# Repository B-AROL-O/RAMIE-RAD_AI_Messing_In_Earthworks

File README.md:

---
title: RAMIE-RAD AI Messing In Earthworks
emoji: 🐨
colorFrom: gray
colorTo: pink
sdk: gradio
sdk_version: 5.49.1
app_file: app.py
pinned: false
license: cc-by-sa-4.0
short_description: A local Gradio MCP server controlling a robot platform
tags:
  - mcp-in-action-track-creative
---

# RAMIE

- **Radical**
- **AI**
- **Messing**
- **In**
- **Earthworks**

A local Gradio MCP AI powered wheeled robot, capable of listening, speaking and executing commands, in the vision of the B-AROL-O team

*TRIVIA: The B-AROL-O team likes to use names of Italian wines as acronyms for robots. [RAMIE](https://nebbiaeluce.com/producer/ramie-perosa-argentina/) is a local red wine from my village*

*TRIVIA: "Vino" is the Italian word for Wine. Intel OpenVINO AI runtime is the perfect runtime to run a robot named after an italian wine by italian developers*

## Scope

The scope of this repository is to document the Hugging Face MCP 1° birthday hackathon

The scope of this repository is to document all instruction to replicate in full the robot project

Work is divided in two parts:

- Work that is qualifying for the hackathon itself, that was started 2025-11-14, this includes learning GRADIO, learning MPC, preparing the MCP tools, interfacing ollama with AI models needed

- Work that is not qualifying for the hackathon and was recycled from previous projects and is in this repository in order to make a complete set of instructions to replicate this project. This include the electronics, the mechanical part of the robot, learning the compute board, and learning that was done for ollama testing of the microphone

This felt like a good chance to gather all the disparate documentation and work done over the years in one tidy set of insttructions that can be followed to make one complete platform end to end with the GRADIO/MCP/OLLAMA software being the keystone that glue it all together.

# Documentation

Designs marked with '*(not qualifying for hackathon)* ' are older recycled design that are here for documentation, instruction and completeness purposes and are not qualifying for the scope of the hackathon.  They are either taken as is, or lightly/heavily adapted to serve for the scope of the Hackathon.

## Mechanical Design

I design in OpenSCAD as I like making geometries as code and I like doing everything parametric.

I decided that the robots should be powered by 18650 batteries. Target configuration is 2S2P. For RAMIE I went with an inverted design that is soldered 4S1P to get 14.8V nominal voltage to be compatible with the input regulator for the Latte Panda Lite Board.

- [MEC: 18650 Battery Holder](/Mechanical/Battery%20Holder%2018650%20OpenSCAD) *(not qualifying for hackathon)*
- [MEC: Wheeled Platform](/Mechanical/Wheeled%20Platform%20OpenSCAD) *(not qualifying for hackathon)*

The robot platform is the one I am designing for Latte Panda Lite Board powered AI robots, it was a good fit for this hackathon

## Board Motor Screen

Interfaces with a UART bidirectional link with the SBC, answer to a serial protocol, controls two servos and a LCD screen. Choosen because I had a bounch assembled in a drawer and working firmware to start from.

- [ELN: Board Motor Screen](/Electronics/Board%20motor%20screen) *(not qualifying for hackathon)*
- [FW: Board Motor Screen](/Firmware/Motor%20Board%20Atmel%20AT324PA) *(not qualifying for hackathon)*
- [FW: Test Bench Serial Communication](/Firmware/Test%20Bench%20Parser) *(not qualifying for hackathon)*
- [FW: Test Bench Motion Orchestrator](/Firmware/Test%20bench%20motion%20orchestration)
- [SW: Python demos to test communication between Host computer and board](/Software/Demo_Host_Serial_Communication/)
- [SW: Python demos to test communication between SBC and board](/Software/Demo_SBC_Serial_Communication/)

# SBC Latte Panda Mu N100 16GB

I lost count of the SBCs I tested for my ultimate goal of making a general robot that expresses a degree of general intelligence with local compute only. The N100 16GB could be it, it has the memory, bandwidth, compute and power envelope to run useful LLMs on the go.

## Luckfox PicoKVM

I always have trouble accessing SBC headless, I finally got a 49€ KVM to mitigate the issue and free myself from using discrete keyboard and mouse

[Luckfox PicoKVM Instructions](/Software/Luckfox%20PicoKVM)

## INSTALL UBUNTU

Install Ubuntu 24.04 Server LTS on the SBC and configure network and storage

[Ubuntu 24.04 Server Install Instructions](/Software/Ubuntu%2024_04%20server%20LTS)

## Luckfox PicoKVM

I always have trouble accessing SBC headless, I finally got a 49€ KVM to mitigate the issue and free myself from using discrete keyboard and mouse

[Luckfox PicoKVM Instructions](/Software/Luckfox%20PicoKVM)

## TTYS0 SSH PUTTY SERIAL

Configure the GRUB to use ttyS0 as UART serial interface to let the host connect via putty via USB to UART FTDI adapter

[TTYS0 SERIAL GRUB CONFIGURATION](/Software/ttys0%20SSH)

## VS Code Remote

Use VS code on host machine with remote SSH plugin to evelop and run code directly on the SBC via WiFi radio

[VS Code Remote Instructions](/Software/VS%20Code%20Remote%20Development%20on%20SBC)

# Battery Teleoperation SSH WiFI

Final test with the robot under battery power with SBC, AT324, WiFI and motors running with SSH teleoperation form keyboard

https://github.com/user-attachments/assets/86d634cf-5507-45de-8ebf-013d29c1c32a

# Ollama GRADIO LLamaindex

The robot hosts and run locally GRADIO

There are two chats

One is the chat to ask about RAMIE capability using LLamaindex to rag the specifications

The second has a tool that attaches with a MCP tool to the motors and genereate serial command for the robot to execute

# Contributors

- [Orso Eric](https://github.com/OrsoEric)

## Useful Links

- [Huggingface Hackathon](https://huggingface.co/MCP-1st-Birthday) 
- [Huggingface Example Track 2 Creative](https://huggingface.co/spaces/ysharma/sample5-hackathon-space-submission/blob/main/README.md)
- [Huggingface space](https://huggingface.co/spaces/MCP-1st-Birthday/RAMIE-RAD_AI_Messing_In_Earthworks)
- [Huggingface Organization](https://huggingface.co/RAMIE-RAD-AI-Messing-In-Earthworks)
- [Github repository](https://github.com/B-AROL-O/RAMIE-RAD_AI_Messing_In_Earthworks)
- [Github project board](https://github.com/orgs/B-AROL-O/projects/5)

## TRACK

Track 2: MCP in Action

mcp-in-action-track-creative

# Copyright and License

Copyright (C) 2025, B-AROL-O Team, all rights reserved.

NOTE: This repository is based upon https://github.com/arol-polito/python-project-template.
Source code license

The source code contained in this repository and the executable distributions are licensed under the terms of the MIT license as detailed in the LICENSE file.
Documentation license

CC BY-SA 4.0

Please note that your contribution to the project Documentation is licensed under a Creative Commons Attribution-Share Alike 4.0 License. see https://creativecommons.org/licenses/by-sa/4.0/

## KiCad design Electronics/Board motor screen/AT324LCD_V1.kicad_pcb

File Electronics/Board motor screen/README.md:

# Motor Board

This is a board that I designed in 2012 to control robots

It was convenient for me to use this board as I have a bounch of them assembled

It has an Atmel AT324PA PDIP40, an ISP programmer, power and breaks out all the pins

I also have a more recent board based on Atmel 4809 in SMD package, both work for this application.

## Gerber

### Bottom Side

### Top Side

### Top Components 

### Bot Components 

### Assembled Powered Flashed

## Adapters

For going to the board I soldered a number of adapters

### Adapter - Pinstrip to Eight Servo

TODO

### Adapter - Pinstrip to Screw COnnector

TODO

## BOM - Bill of Material

TODO

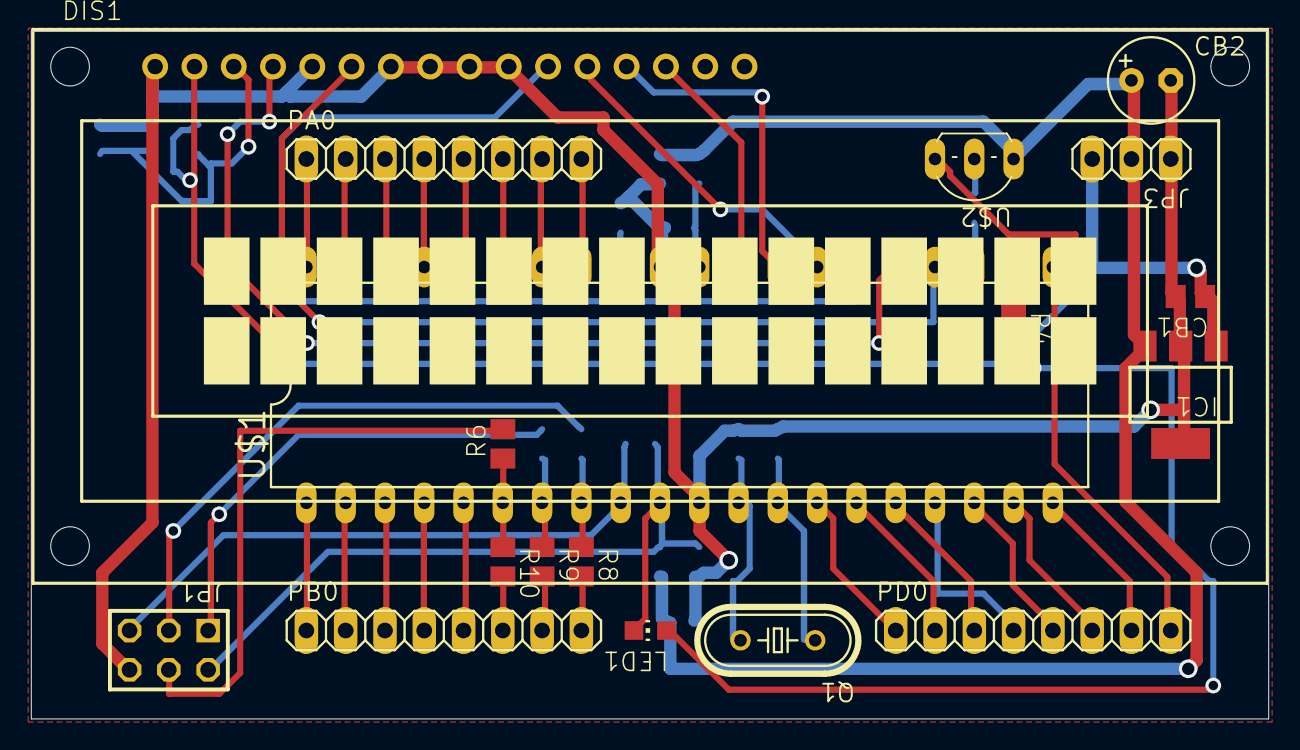
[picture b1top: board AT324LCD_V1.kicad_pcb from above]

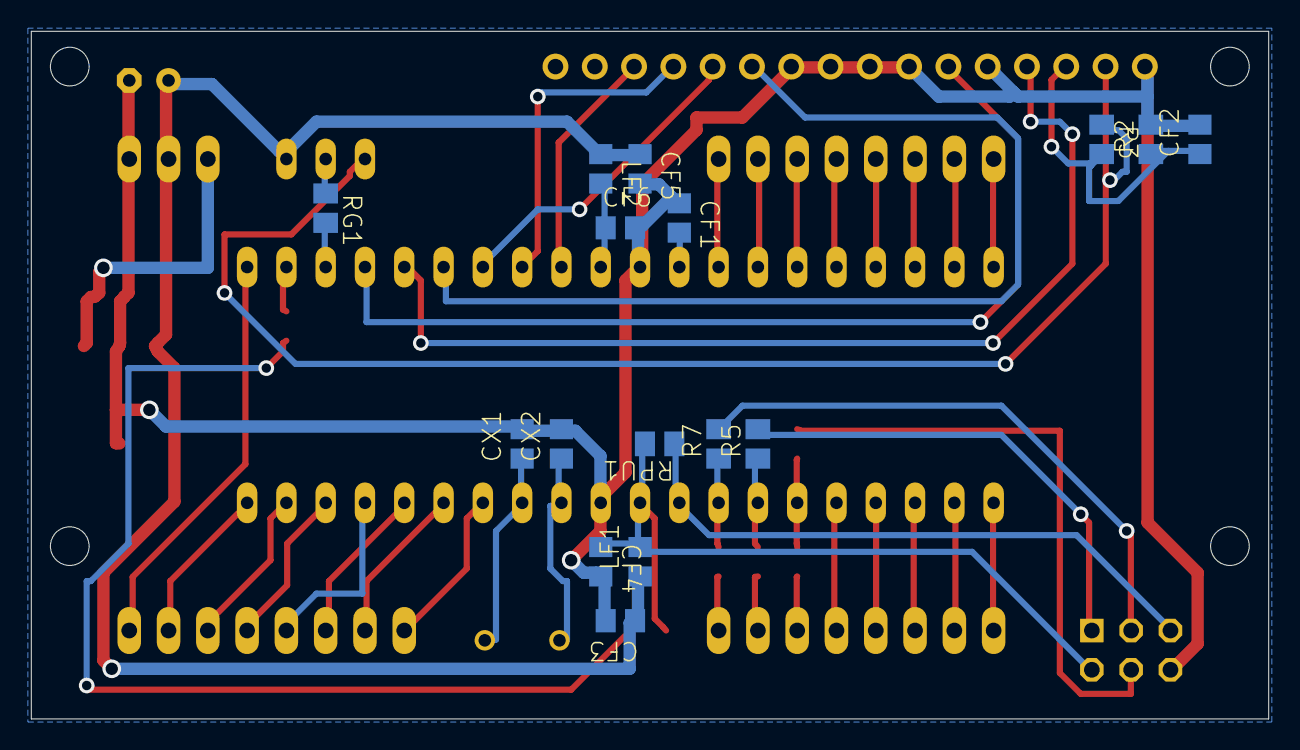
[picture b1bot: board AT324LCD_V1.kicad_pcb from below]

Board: 16 copper layers, 80.0 x 44.5 mm, 34 parts (16 on the bottom side), 51 nets.

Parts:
CB1: 1u; C0805
CB2: 100u; E2,5-6
CF1, CF2: 10n; C0805
CF3, CF4, CF5, CF6: 100n; C0805
CX1, CX2: 22p; C0805
DIS1: TUXGR_16X2_R2
IC1: SOT223
JP1: AVR-ISP-6
JP3: 1X03
LED1: CHIP-LED0805
LF1, LF2: 600; L0805
PA0: 1X08
PB0: 1X08
PD0: 1X08
Q1: 20M; HC49_S
R2, R5, R6, R7, R8, R9, R10: 1k; M0805
R3: 8.2k; M0805
R4: 330; M0805
RG1: 4.7; M0805
RPU1: 8.2k; M0805
U$1: MEGA324PDIL40; DIL40
U$2: ZVP2106TO92; TO92-

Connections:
D4: DIS1.11, U$1.26
D5: DIS1.12, U$1.27
D6: DIS1.13, U$1.28
D7: DIS1.14, U$1.29
EN: DIS1.6, U$1.24
GND: CB1.2, CB2.-, CF1.1, CF2.2, CF3.2, CF4.2, CF5.2, CF6.2, CX1.2, CX2.2, DIS1.1, DIS1.5, DIS1.7, DIS1.8, DIS1.9, DIS1.10, IC1.2, IC1.4, JP1.6, JP3.1, R2.2, U$1.11, U$1.31
LCDEN#: RG1.2, U$1.23
LED: R4.1, U$1.22
unnamed: CF1.2, U$1.32
unnamed: CX1.1, Q1.1, U$1.13
unnamed: CX2.1, Q1.2, U$1.12
unnamed: PB0.8, R8.2
unnamed: RG1.1, U$2.2
unnamed: CF2.1, DIS1.3, R2.1, R3.2
unnamed: LED1.A, R4.2
unnamed: PB0.7, R9.2
unnamed: PB0.6, R10.2
unnamed: JP1.1, R5.2
unnamed: JP1.4, R6.2
unnamed: JP1.3, R7.2
PA0: PA0.1, U$1.40
PA1: PA0.2, U$1.39
PA2: PA0.3, U$1.38
PA3: PA0.4, U$1.37
PA4: PA0.5, U$1.36
PA5: PA0.6, U$1.35
PA6: PA0.7, U$1.34
PA7: PA0.8, U$1.33
PB0: PB0.1, U$1.1
PB1: PB0.2, U$1.2
PB2: PB0.3, U$1.3
PB3: PB0.4, U$1.4
PB4: PB0.5, U$1.5
PB5: R6.1, R10.1, U$1.6
PB6: R5.1, R9.1, U$1.7
PB7: R7.1, R8.1, U$1.8
PD0: PD0.1, U$1.14
PD1: PD0.2, U$1.15
PD2: PD0.3, U$1.16
PD3: PD0.4, U$1.17
PD4: PD0.5, U$1.18
PD5: PD0.6, U$1.19
PD6: PD0.7, U$1.20
PD7: PD0.8, U$1.21
RS: DIS1.4, U$1.25
RST#: JP1.5, RPU1.1, U$1.9
VADC: CF6.1, LF2.2, U$1.30
VIN: CB1.1, IC1.1, JP3.3
VIN5: CB2.+, CF3.1, CF5.1, IC1.3, JP3.2, LF1.1, LF2.1, U$2.3
VLCD: DIS1.2, R3.1, U$2.1
VUC: CF4.1, JP1.2, LED1.C, LF1.2, RPU1.2, U$1.10

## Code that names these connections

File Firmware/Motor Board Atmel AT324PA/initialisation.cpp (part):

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	///	configure the related I/O pin as output
	///**********************************************************************

	//PA0			: Servo 0
	//PA1			: Servo 1
	//PA2			: Servo 2
	//PA3			: Servo 3
	//PA4			: Servo 4
	//PA5			: Servo 5
	//PA6			: Servo 6
	//PA7			:
	PORT_A_CONFIG('L','L','L','L','L','L','L','L');
	

	//PB0			:
	//PB1			:
	//PB2			:
	//PB3			:
	//PB4			:
	//PB5			:
	//PB6			:
	//PB7			:
	PORT_B_CONFIG('R','R','R','R','R','R','R','R');

	//PC0			: LED#
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	//PC7			: LCD_D7
	PORT_C_CONFIG('H','H','L','L','L','L','L','L');

	//PD0			: UC_RXI SBC_TXO 
	//PD1			: UC_TXO SBC_RXI
	//PD2			: 
	//PD3			:
	//PD4			:
	//PD5			:
	//PD6			:
	//PD7			:
	PORT_D_CONFIG('R','H','R','R','R','R','R','R');

	///**********************************************************************
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
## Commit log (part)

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2025-11-14 Update README with Huggingface and GitHub links
    Added links to Huggingface space, organization, and GitHub repository.
2025-11-15 Adding github project and partecipant
2025-11-15 add ,.license
2025-11-15 Added link for track Added folder structure
2025-11-15 added readme to folder structure
2025-11-15 This is a board that I designed in 2012 to control robots It was convenient for me to use this board as I have a bounch of them assembled It has an Atmel AT324PA, an ISP programmer, power and breaks 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
2025-11-15 Added images and documentation for the motor control board
2025-11-15 Adapted from Unit Zero (2019) and Industrious Resonance (2025)
    Firmware to control the motor Board
    PPM signal for continuous rotation servo motors
    LCD screen with parallel protocol
    UART link to communicate with SBC
    TODO: Develop a communication protocol that works with MCP server GRADIO
    https://github.com/B-AROL-O/RAMIE-RAD_AI_Messing_In_Earthworks/issues/5
2025-11-15 Added firmware links to the main README Added some more description on the readme https://github.com/B-AROL-O/RAMIE-RAD_AI_Messing_In_Earthworks/issues/5 https://github.com/B-AROL-O/RAMIE-RAD_AI_Mess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
2025-11-15 Added documentation of the firmware
    https://github.com/B-AROL-O/RAMIE-RAD_AI_Messing_In_Earthworks/issues/5
2025-11-15 Test bench for the serial communicaton and callback function on Firmware https://github.com/B-AROL-O/RAMIE-RAD_AI_Messing_In_Earthworks/issues/5
2025-11-15 linked test bench readme on the main readme https://github.com/B-AROL-O/RAMIE-RAD_AI_Messing_In_Earthworks/issues/1
2025-11-15 Added the codeblock test bench for motion orchestration class. https://github.com/B-AROL-O/RAMIE-RAD_AI_Messing_In_Earthworks/issues/5
2025-11-15 OpenSCAD Holder for 18650 batteries developed over several years
    Configurations
    - 1S1P
    - 2S1P
    - 2S2P
    - 2S2P upside down
    https://github.com/B-AROL-O/RAMIE-RAD_AI_Messing_In_Earthworks/issues/10
2025-11-15 Fixed readme for the battery holder https://github.com/B-AROL-O/RAMIE-RAD_AI_Messing_In_Earthworks/issues/10 https://github.com/B-AROL-O/RAMIE-RAD_AI_Messing_In_Earthworks/issues/1
2025-11-15 OpenSCAD design of the platform This is recycled from Industrious Resonance that is already a Latte Panda Mu platform under development I do need to refine it as it was not finished https://github.co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
2025-11-15 Added images of the design process of the wheeled platform. This was lots of work I did for Industrious Resonance but it worked out great I have a pivot ping pong ball, HS422 servo holders, all tolle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
    TODO: geometry for the electronics and details. I decided to print an intermediate step.
2025-11-15 Added documentation of the platform design process and updated readme https://github.com/B-AROL-O/RAMIE-RAD_AI_Messing_In_Earthworks/issues/8
2025-11-15 BUG: if I have a command with argument VR%L% and a command VR%L%T% the parser gets confused and cannot match.
2025-11-15 doesn't compile. something with C++? -.-
2025-11-15 I rebuilt the AVR project using the C++ compiler and it compiles and load now Much bigger executable from 3 to 9KB so it's doing more Linked the parser Seems to be doing something But the serial deco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
2025-11-15 FRACK YEAH it works! I had just some issue with initialization. Done a video and tested ping and speed commands and they work. The F signature command doesn't, it's likely an infinite loop. I didn't 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
    https://github.com/B-AROL-O/RAMIE-RAD_AI_Messing_In_Earthworks/issues/5
2025-11-15 https://github.com/B-AROL-O/RAMIE-RAD_AI_Messing_In_Earthworks/issues/1
2025-11-16 Remove borked project and rename the working project
2025-11-16 Fixed SIGN and REV messages. Added aid function to send strings. https://github.com/B-AROL-O/RAMIE-RAD_AI_Messing_In_Earthworks/issues/5
    Documentation for the communication protocol.
    https://github.com/B-AROL-O/RAMIE-RAD_AI_Messing_In_Earthworks/issues/6
2025-11-16 DEMO 3 The code sends every 250ms increase speed on R by increment of 10 up to 50 Then decrement in speed -10 down to -50 then increment of +10 up to 0 then do the same on L speed repeat
    https://github.com/B-AROL-O/RAMIE-RAD_AI_Messing_In_Earthworks/issues/15
2025-11-16 Linked Python demo to the board section main README https://github.com/B-AROL-O/RAMIE-RAD_AI_Messing_In_Earthworks/issues/1 https://github.com/B-AROL-O/RAMIE-RAD_AI_Messing_In_Earthworks/issues/15
2025-11-16 Added a demo inside the firmware that loads commands into the UART RX buffer directly
    This way I can test the parser without using the terminal.
    https://github.com/B-AROL-O/RAMIE-RAD_AI_Messing_In_Earthworks/issues/18
2025-11-16 adding an executed command counter on the LCD importing the motion orchestration c++ library
2025-11-16 implemented //Enumerates modes of operation of the servo motors enum E_servo_mode { //Direct speed mode will sustain the speed given until different instruction SERVO_SPEED_MODE, //Timed servo mode w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
    when sending a direct speed command goes into DS and sustain last speed
    when sending a timed speed, goes into TS mode and use the orchestrator, if the queue is empty, it stops moving
    https://github.com/B-AROL-O/RAMIE-RAD_AI_Messing_In_Earthworks/issues/18
2025-11-16 Orchestrator is linked but seems not to be working...
2025-11-16 Firmware for motion orchestration done, filmed video Showed switch between DS and TS Showed loading of the queue and timed execution
    https://github.com/B-AROL-O/RAMIE-RAD_AI_Messing_In_Earthworks/issues/18
2025-11-16 Added images and videos of the testing for the firmware and serial interface
    https://github.com/B-AROL-O/RAMIE-RAD_AI_Messing_In_Earthworks/issues/18
2025-11-17 Used kicad to convert and measure the AT324 board In Openscad modelling the sloped support wall Done the trigonometry to decide on the board angle
2025-11-17 Building the mechanical support for AT324 I did a lot of fancy trigonometry to find where to drill
2025-11-17 Did precision drills for the screw! TODO: Now I just need to tip them with an hole for the nut
2025-11-17 Added initial MCP server implementation with greet, manifest and capabilities tools
2025-11-17 Added brief guide to run mcp server
2025-11-18 completed wall with slope and drill with all fancy trigonometry nailed down. made it into a shape library created the box model for the AT324 LCD board
2025-11-18 committing geometry done on bus.
2025-11-18 constructed sloped support walls for the AT324 module updated README TODO: add drills for a bolt for power
2025-11-18 I added an hole on the support for power bolts i generated stl so i can print the shape_wall_sloped_with_bolt_nut and hot glue them to the robot for fun and profit
2025-11-19 Printed support for AT324 with hotglue Failed print but okay for prototype Added photos for other sections https://github.com/B-AROL-O/RAMIE-RAD_AI_Messing_In_Earthworks/issues/21
2025-11-19 added documentation for electronics connection of LPMU
2025-11-19 trying and failing to setup wifi https://github.com/B-AROL-O/RAMIE-RAD_AI_Messing_In_Earthworks/issues/27
2025-11-20 updating readme about protocol and architecture
2025-11-20 improved documentation for the communication protocol
2025-11-20 tested possible system prompt for trajectories on Gemma 3 4B Q4 Vision Instruct. it's mhe it does generate mostly valid strings but it cannot count right and it does exceed the argument parameters at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
2025-11-21 FRACK!!! So I added LM Studio inference to Alessio code expecting it to tool call it doesn't, the fracker just prints outuseless code to do manually a tool call. it turns out Gemma 3 4B Q4 Vision Ins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
    Gemma (and most llama.cpp based models) can’t interpret the functions/tool_calls protocol that OpenAI’s GPT‑4 or Anthropic’s Claude use.
    They only generate code or textual hints, which is why you see the tool_code block.
    Your client didn’t act on a too
2025-11-21 Qwen 3 4B Q4 vision instruct tool has tool calling and complies with my specs tested, logged still doesn't call tools. OSS20B has vibecoded new code to try
2025-11-22 I was trying to resurrect the N100 16GB Server Passive to no avail
    I worked on the N100 8GB Desktop Active
    I need to modify grub to activate the serial
    Speed 9600 and 115200 work
    Speed 250000 doesn't and default to 9600
    Putty serial connection work. Terminal serial view dump works
    I cannot resurrect the bricked board since I need to modify grub and i'm locked out hard.
2025-11-22 Tested Luckfox PicoKVM and it's painless
    Made documentation for the KVM
    Added reference to main readme and software readme
    https://github.com/B-AROL-O/RAMIE-RAD_AI_Messing_In_Earthworks/issues/30
2025-11-22 I put the LP MU 8GB with active cooling on the robot
    I burned a new operating system replacing the desktop version
    Did extensive guide of the installation, hopefully fixing network and drive problems
    https://github.com/B-AROL-O/RAMIE-RAD_AI_Messing_In_Earthworks/issues/27
2025-11-22 Updated main readme
    https://github.com/B-AROL-O/RAMIE-RAD_AI_Messing_In_Earthworks/issues/27
2025-11-22 added image of KVM on main readme
2025-11-22 Configure the GRUB to use ttyS0 as UART serial interface to let the host connect via putty via USB to UART FTDI adapter
    Added documentation and instructions
    Added link to main readme
    https://github.com/B-AROL-O/RAMIE-RAD_AI_Messing_In_Earthworks/issues/29
2025-11-23 Reorganized software and main readme
    https://github.com/B-AROL-O/RAMIE-RAD_AI_Messing_In_Earthworks/issues/1
2025-11-23 Installation of UV Creation of TOML UV venv Enumeration of serial ports
    ```
    uv run demo_1_enumerate_serial.py
    Using CPython 3.14.0
    Creating virtual environment at: .venv
    Installed 1 package in 16ms
    /home/sona/Demo 2 - Serial Communication SBC/.venv/lib/python3.14/site-packages/serial/__init__.py
2025-11-23 Creating folder for application installing UV creating scripts giving permission to ports
    BUG I can scan the ports, but I'm not getting an answer, why?
    https://github.com/B-AROL-O/RAMIE-RAD_AI_Messing_In_Earthworks/issues/32
2025-11-23 This was not straightforward I had to go deep with oscilloscope to find out why the python link from SBC to AT324 wasn't working while it was working fine under windows It turns out linux has discret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
    I moved application to 115200 b/s
    I moved the firmware to 113636 b/s
    Now it communicates fine.
    I'll need to significantly accelerate the communication for the future
    I need to find discrete steps that work both on linux, and on firmware
    because on firmware I have a lower clock that gives me wider steps due to prescaler settings
2025-11-23 DEMO from 1 to 4 run fine directly on SBC communicating with AT324 and moving motors
    https://github.com/B-AROL-O/RAMIE-RAD_AI_Messing_In_Earthworks/issues/32
2025-11-23 Reordered files, updated readme
    https://github.com/B-AROL-O/RAMIE-RAD_AI_Messing_In_Earthworks/issues/32
2025-11-23 This was easy, console application to move robot when keys are pressed.
    Next the big one, do it all from battery power.
    https://github.com/B-AROL-O/RAMIE-RAD_AI_Messing_In_Earthworks/issues/22
2025-11-23 Add image and video of RAMIE roaming teleoperated
    https://github.com/B-AROL-O/RAMIE-RAD_AI_Messing_In_Earthworks/issues/34
2025-11-23 Added on eln and main readme the video
    https://github.com/B-AROL-O/RAMIE-RAD_AI_Messing_In_Earthworks/issues/34
    Issue with powering SBC. WHY?=???
    https://github.com/B-AROL-O/RAMIE-RAD_AI_Messing_In_Earthworks/issues/35
2025-11-29 Install Ollama and test inference
    https://github.com/B-AROL-O/RAMIE-RAD_AI_Messing_In_Earthworks/issues/37
2025-11-29 upload script
2025-11-29 gradio 6 application interface locally with ollama added MCP tool to generate motion trajectory
2025-11-29 finally interfaced GRADIO with the robot and it works
2025-11-30 upload to HF
2025-11-30 Track mp4 files with Git LFS
2025-11-30 Move large video files to Git LFS
2025-11-30 fix(README): fix typo in documentation
    s/hackaton/hackathon/
2025-11-30 Added workflow to sync github repo with HF repo
